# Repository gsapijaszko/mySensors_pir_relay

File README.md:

# mySensors_pir_relay
PIR/light relay with nRF24 radio, mySensors network

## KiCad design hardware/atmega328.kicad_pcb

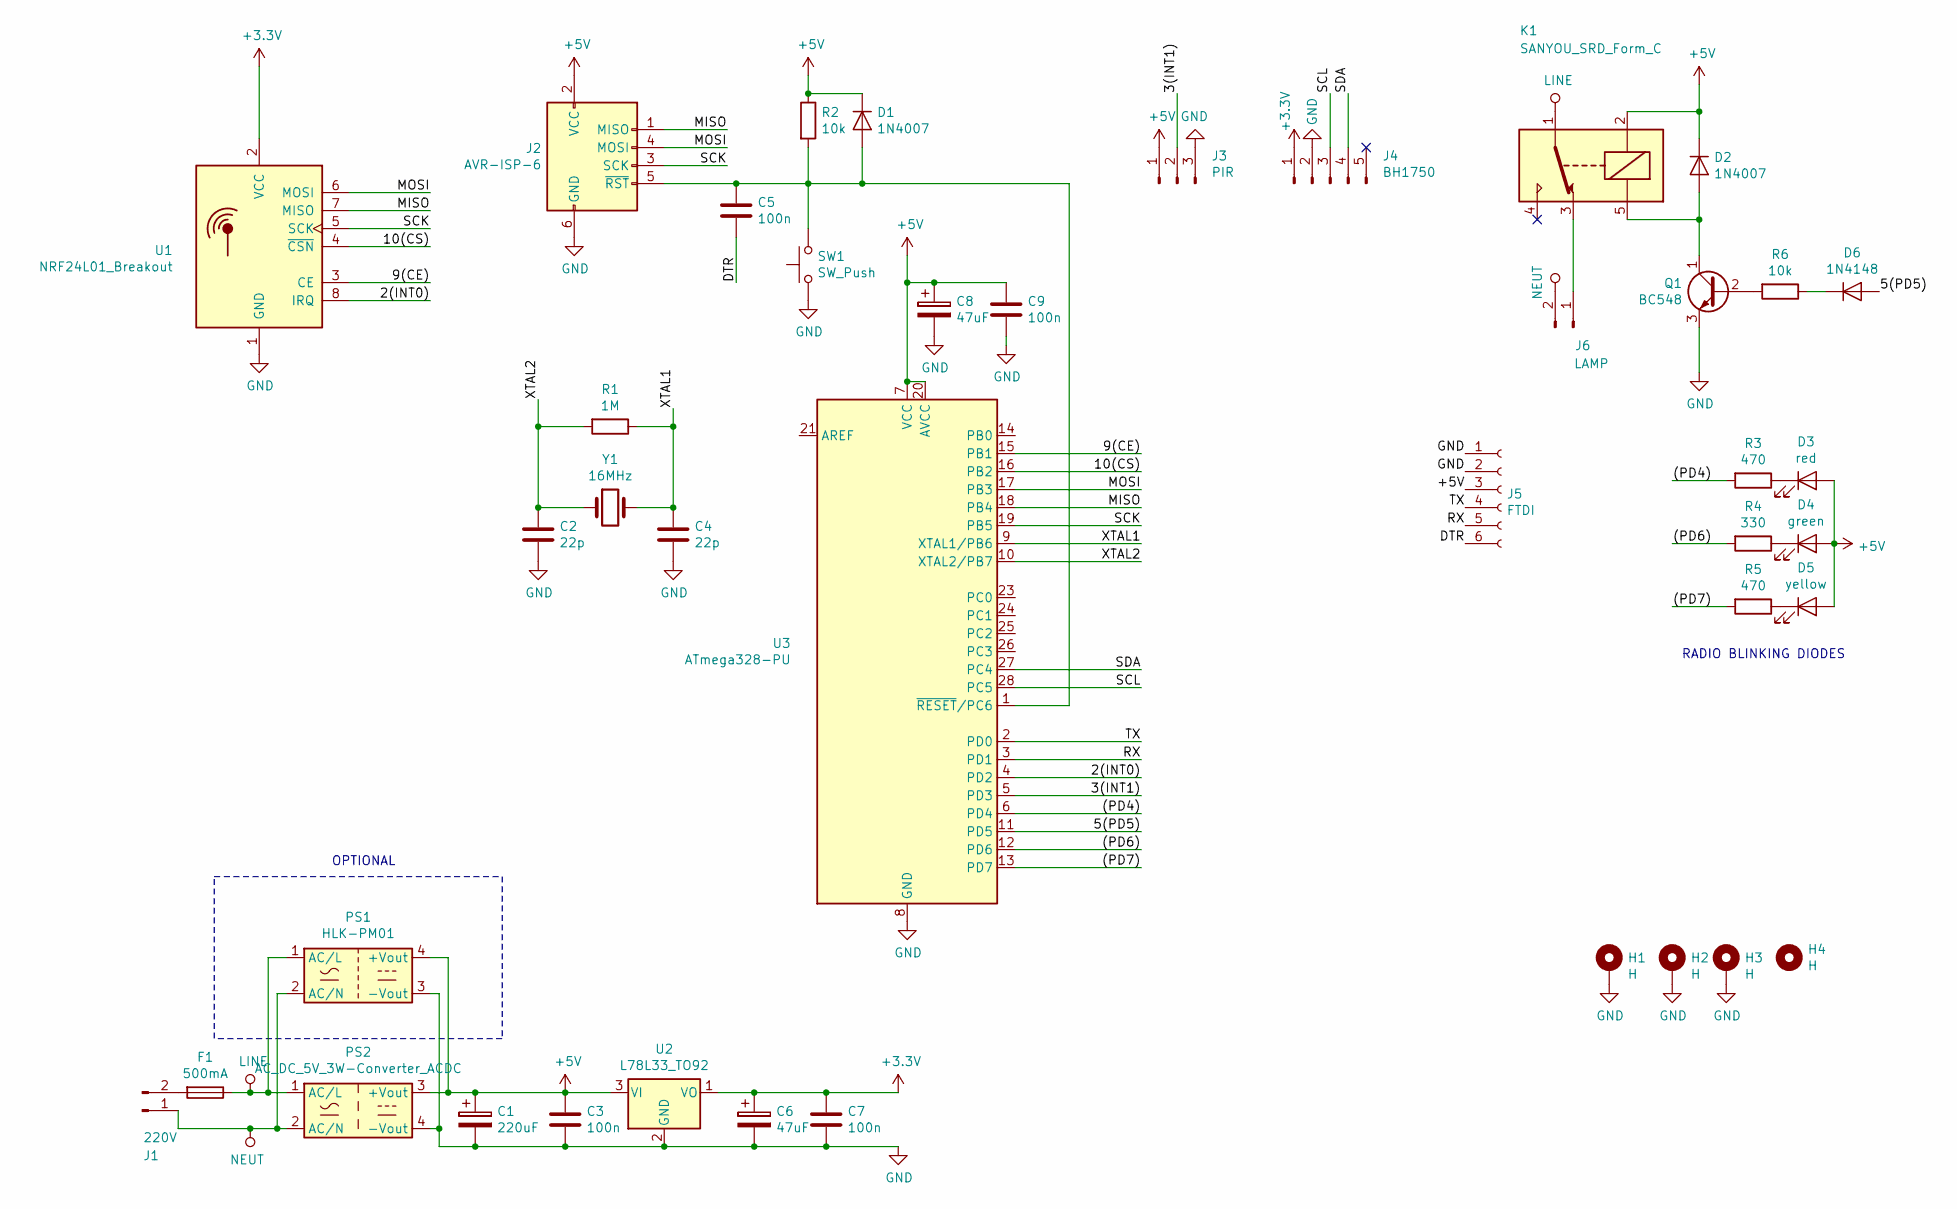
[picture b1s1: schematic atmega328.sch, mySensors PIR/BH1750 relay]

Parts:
C1: 220uF; CP_Radial_D8.0mm_P3.50mm
C2, C4: 22p; C_Disc_D3.8mm_W2.6mm_P2.50mm
C3, C5, C7, C9: 100n; C_Disc_D5.1mm_W3.2mm_P5.00mm
C6, C8: 47uF; CP_Radial_D5.0mm_P2.00mm
D1, D2: 1N4007; D_DO-41_SOD81_P10.16mm_Horizontal
D3: red; LED_D5.0mm_Horizontal_O3.81mm_Z9.0mm
D4: green; LED_D5.0mm_Horizontal_O3.81mm_Z9.0mm
D5: yellow; LED_D5.0mm_Horizontal_O3.81mm_Z9.0mm
D6: 1N4148; D_DO-34_SOD68_P7.62mm_Horizontal
F1: 500mA; Fuseholder_TR5_Littelfuse_No560_No460
H1, H2, H3, H4: H; MountingHole_3.5mm_Pad_Via
J1: 220V; KF301-2P-5.0
J2: AVR-ISP-6; IDC-Header_2x03_P2.54mm_Vertical
J3: PIR; KF2510-A-3P-M-TH-V
J4: BH1750; KF2510-A-5P-M-TH-V
J5: FTDI; PinSocket_1x06_P2.54mm_Vertical
J6: LAMP; KF301-2P-5.0
K1: SANYOU_SRD_Form_C; Relay_SPDT_SANYOU_SRD_Series_Form_C
PS1: HLK-PM01; Converter_ACDC_HiLink_HLK-PMxx
PS2: AC_DC_5V_3W-Converter_ACDC; AC_DC_5V_3W
Q1: BC548; TO-92_Inline_Wide
R1: 1M; R_Axial_DIN0207_L6.3mm_D2.5mm_P10.16mm_Horizontal
R2: 10k; R_Axial_DIN0207_L6.3mm_D2.5mm_P5.08mm_Vertical
R3, R5: 470; R_Axial_DIN0207_L6.3mm_D2.5mm_P5.08mm_Vertical
R4: 330; R_Axial_DIN0207_L6.3mm_D2.5mm_P5.08mm_Vertical
R6: 10k; R_Axial_DIN0207_L6.3mm_D2.5mm_P10.16mm_Horizontal
SW1: SW_Push; SW_Tactile_SKHH_Angled
U1: NRF24L01_Breakout; nRF24L01_Breakout
U2: L78L33_TO92; TO-92
U3: ATmega328-PU; DIP-28_W7.62mm
Y1: 16MHz; Crystal_HC49-4H_Vertical

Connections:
+3V3: C6.1, C7.1, J4.1, U1.2 (VCC), U2.1 (VO)
+5V: C1.1, C3.1, C8.1, C9.1, D1.1 (K), D2.1 (K), D3.2 (A), D4.2 (A), D5.2 (A), J2.2 (VCC), J3.1, J5.3, K1.2, PS1.4 (+Vout), PS2.3 (+Vout), R2.1, U2.3 (VI), U3.7 (VCC), U3.20 (AVCC)
/2(INT0): U1.8 (IRQ), U3.4 (PD2)
/3(INT1): J3.2, U3.5 (PD3)
/5(PD5): D6.2 (A), U3.11 (PD5)
/9(CE): U1.3 (CE), U3.15 (PB1)
/10(CS): U1.4 (~CSN), U3.16 (PB2)
/(PD4): R3.2, U3.6 (PD4)
/(PD6): R4.2, U3.12 (PD6)
/(PD7): R5.2, U3.13 (PD7)
/DTR: C5.2, J5.6
/MISO: J2.1 (MISO), U1.7 (MISO), U3.18 (PB4)
/MOSI: J2.4 (MOSI), U1.6 (MOSI), U3.17 (PB3)
/RX: J5.5, U3.3 (PD1)
/SCK: J2.3 (SCK), U1.5 (SCK), U3.19 (PB5)
/SCL: J4.3, U3.28 (PC5)
/SDA: J4.4, U3.27 (PC4)
/TX: J5.4, U3.2 (PD0)
/XTAL1: C4.1, R1.1, U3.9 (XTAL1/PB6), Y1.2
/XTAL2: C2.1, R1.2, U3.10 (XTAL2/PB7), Y1.1
GND: C1.2, C2.2, C3.2, C4.2, C6.2, C7.2, C8.2, C9.2, H1.1, H2.1, H3.1, J2.6 (GND), J3.3, J4.2, J5.1, J5.2, PS1.3 (-Vout), PS2.4 (-Vout), Q1.3 (E), SW1.1, U1.1 (GND), U2.2 (GND), U3.8 (GND), U3.22 (GND)
LINE: F1.1, K1.1, PS1.1 (AC/L), PS2.1 (AC/L)
NEUT: J1.1, J6.2, PS1.2 (AC/N), PS2.2 (AC/N)
unnamed: C5.1, D1.2 (A), J2.5 (~RST), R2.2, SW1.2, U3.1 (~RESET~/PC6)
unnamed: D2.2 (A), K1.5, Q1.1 (C)
unnamed: D3.1 (K), R3.1
unnamed: D4.1 (K), R4.1
unnamed: D5.1 (K), R5.1
unnamed: D6.1 (K), R6.1
unnamed: F1.2, J1.2
unnamed: J6.1, K1.3
unnamed: Q1.2 (B), R6.2

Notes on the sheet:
RADIO BLINKING DIODES
OPTIONAL

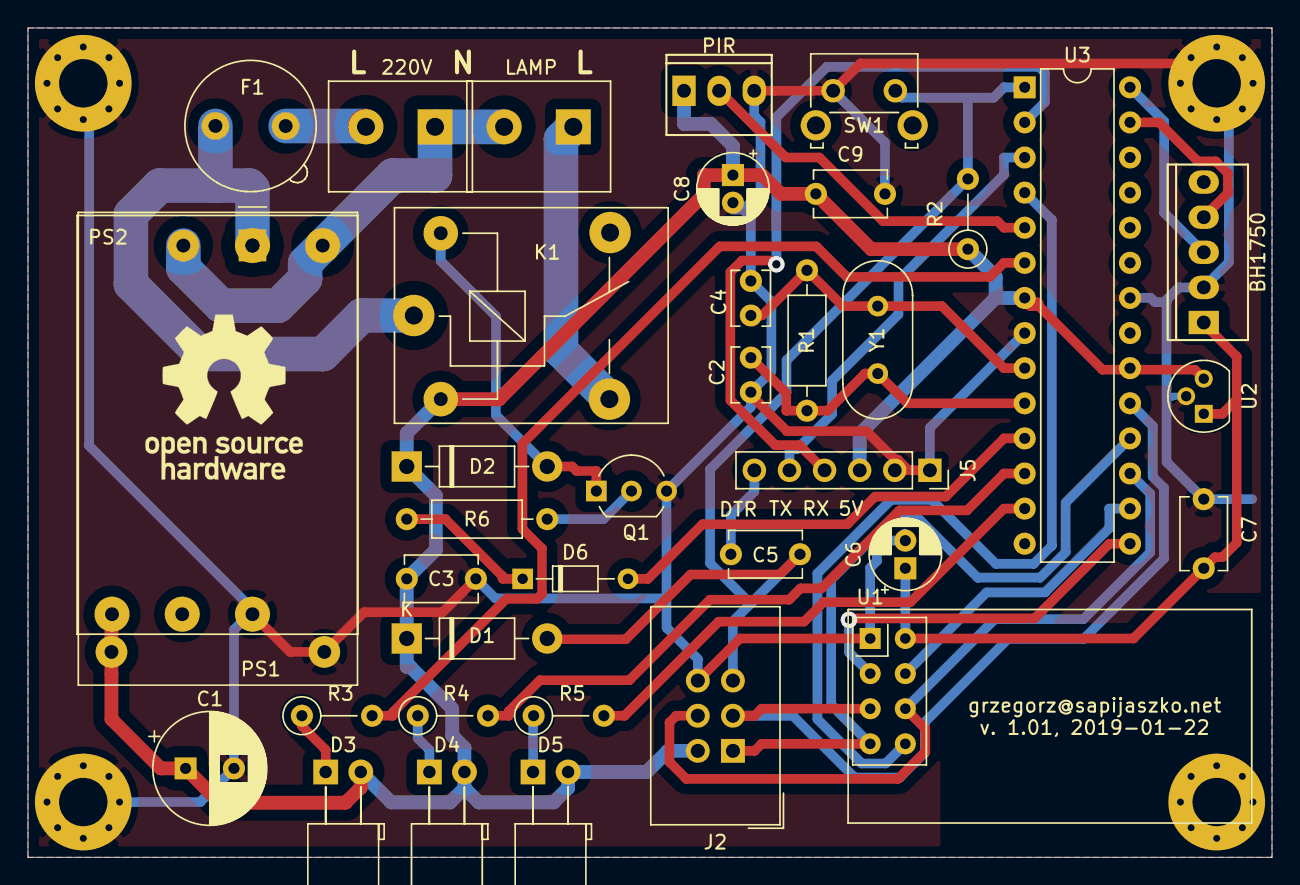
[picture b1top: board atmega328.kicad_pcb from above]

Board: 2 copper layers, 90.0 x 60.0 mm, 41 parts (0 on the bottom side), 32 nets.

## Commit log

2018-12-30 initial commit
    initial commit, based on old solution: arduino pro mini + modules
2018-12-30 hardware added
2018-12-30 case in freecad
2018-12-30 minor updates
2018-12-30 cleanup
2018-12-31 case redrawn
2018-12-31 moved radio up, support added
2019-01-01 another try for case
2019-01-01 Revert "Update case.fcstd, case.fcstd1, and atmega328-rescue.lib"
    This reverts commit 71372981b5001050260e6a5e78be0348375636c0.
2019-01-01 FTDI added, minor adjustments
2019-01-02 Update case.fcstd, case.fcstd1, and 3 more files...
2019-01-03 Update case.fcstd, case.fcstd1, and 14 more files...
2019-01-05 Update case.fcstd, case.fcstd1, and 31 more files...
2019-01-05 Update assembly.fcstd, assembly.fcstd1, and 6 more files...
2019-01-05 Update assembly.fcstd, assembly.fcstd1, and 9 more files...
2019-01-06 Update .gitignore, PIR_sensor.FCStd, and 5 more files...
2019-01-06 Update assembly.fcstd, assembly.fcstd1, and 4 more files...
2019-01-06 Update clip.FCStd, clip.FCStd1, and 3 more files...
2019-01-16 Update atmega328-rescue.dcm, atmega328.kicad_pcb, and 15 more files...
2019-01-18 Update atmega328.bak, atmega328.kicad_pcb, and 5 more files...
2019-01-22 Update _autosave-atmega328.kicad_pcb, atmega328.kicad_pcb, and 13 more files...
2019-01-22 Update _autosave-atmega328.kicad_pcb, atmega328.kicad_pcb, and atmega328.kicad_pcb-bak
2019-01-26 Update LICENSE and fp-info-cache
2019-02-11 revision of diode's resistors
2019-02-11 Update atmega328.kicad_pcb, ibom.html, and fp-info-cache
2019-02-23 Update BottomPart.stl, assembly.fcstd, and 2 more files...
2019-03-30 Update lower_part.fcstd, lower_part.fcstd1, and 2 more files...
2019-12-30 Update case_top.FCStd, case_top.FCStd1, and 3 more files...
2020-01-12 case finished
2020-01-15 Update fp-info-cache
